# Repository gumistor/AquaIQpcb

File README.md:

# AquaIQpcb
Mini computer to control a sea tank. Based on LPC1769Board.

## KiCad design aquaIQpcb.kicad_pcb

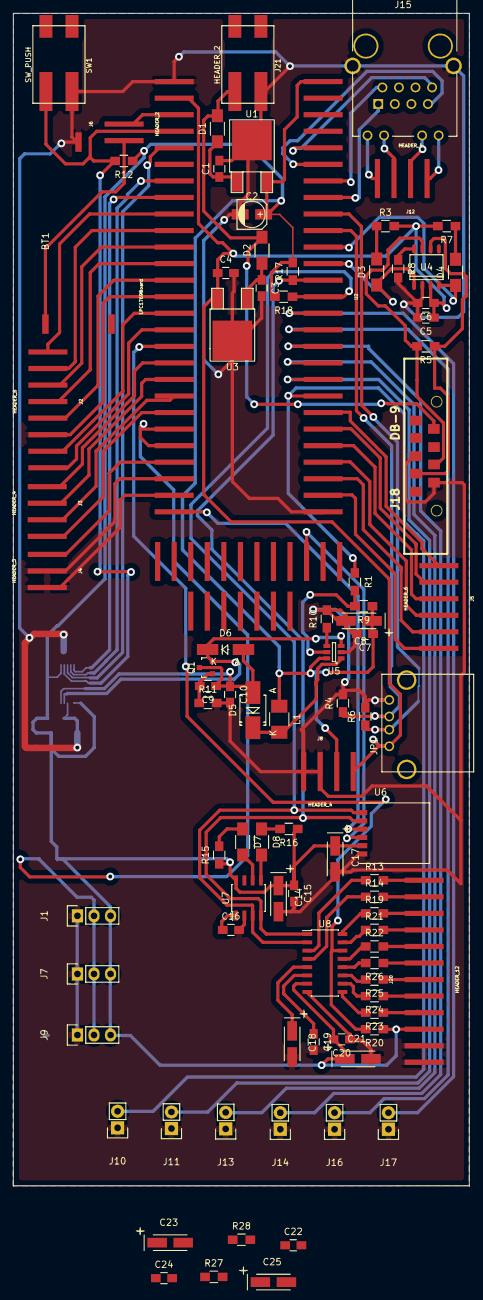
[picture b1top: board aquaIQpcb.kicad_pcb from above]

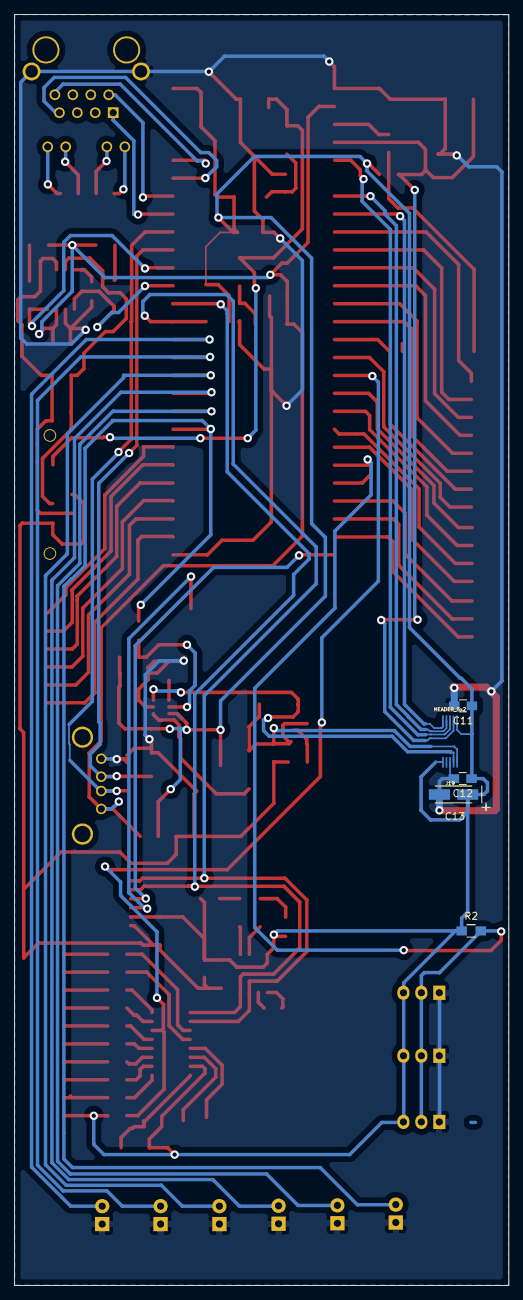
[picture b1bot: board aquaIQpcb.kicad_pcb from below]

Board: 2 copper layers, 70.0 x 180.0 mm, 95 parts (5 on the bottom side), 91 nets.

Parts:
BT1: Battery; BATTERY_3.6_05AA
C1, C3: 330n; C_0805_HandSoldering
C2: 10uF; c_elec_4x5.3
C4, C5, C6, C7, C20, C22: 100n; C_0805_HandSoldering
C8: 22u/6.3V; TantalC_SizeA_EIA-3216_HandSoldering
C9: 47nF; C_0805_HandSoldering
C10: 1u/25V; C_0805_HandSoldering
C11, C12, C15, C16, C19: 100nF; C_0805_HandSoldering
C13, C14, C17: 22uF/6.3V; TantalC_SizeA_EIA-3216_HandSoldering
C18: 2.2uF/5V; TantalC_SizeA_EIA-3216_HandSoldering
C21: 1u; TantalC_SizeA_EIA-3216_HandSoldering
C23: 1uF/6.3V; TantalC_SizeA_EIA-3216_HandSoldering
C24: 10nF; C_0805_HandSoldering
C25: 2.2uF/6.3V; TantalC_SizeA_EIA-3216_HandSoldering
D1, D2: D; R_1206_HandSoldering
D3, D4: LED; R_1206_HandSoldering
D5: D_Schottky; Diode-SMB_Handsoldering
D6: 24V; Diode-MiniMELF_Handsoldering
D7: GREEN; R_1206_HandSoldering
D8: RED; R_1206_HandSoldering
J1, J7, J9: HEADER_3; Pin_Header_Straight_1x03
J2: HEADER_8; HEADER_SMD_1x8
J3, J8, J12: HEADER_4; HEADER_SMD_1x4
J4: HEADER_3; HEADER_SMD_1x3
J5: HEADER_6; HEADER_SMD_1x6
J6: HEADER_2; HEADER_SMD_1x2
J10, J11, J13, J14, J16, J17: HEADER_2; Pin_Header_Straight_1x02
J15: rj45; RJ45_TRANSFO
J18: DB-9; DB9SMD_oneside
J19: HEADER_5x2; HIROSE_DF23C-10
J20: HEADER_12; HEADER_SMD_1x12
J21: HEADER_2; MOLEX_LITETRAPS_2
JP1: USB-A; USB_A
L1: 6.8uH; R_1210_HandSoldering
Q1: MMBT3904; SOT-23
R1: 0R; R_0805_HandSoldering
R2, R17, R18: 4k7; R_0805_HandSoldering
R3, R7: 1k; R_0805_HandSoldering
R4, R6: 15k; R_0805_HandSoldering
R5: 120; R_0805_HandSoldering
R8: 47k; R_0805_HandSoldering
R9, R12, R20: 10k; R_0805_HandSoldering
R10, R11: 1k5; R_0805_HandSoldering
R13, R14, R19, R21, R22: 560; R_0805_HandSoldering
R15, R16, R23, R24, R25, R26: 100; R_0805_HandSoldering
R27, R28: 270; R_0805_HandSoldering
SW1: SW_PUSH; MOLEX_LITETRAPS_2
U1: LF33CDT; DPAK-2
U2: LPC1769Board; LPCXPRESSO_LPC1769
U3: 7805; DPAK-2
U4: MCP2551-I/SN; SO-8
U5: LT1932; SOT-23-6
U6: HP02S
U7: HIH6131; SOIC-8_3.9x4.9mm_Pitch1.27mm
U8: CY8CMBR3110; SOIC-16_3.9x9.9mm_Pitch1.27mm

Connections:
+3V3: C2.1, C7.1, C8.1, C11.1, C12.1, C13.1, C17.1, C20.2, C21.1, C22.2, J1.3, J7.3, J8.3, J9.3, J15.3, J19.1, J19.6, J20.3, L1.1, R2.1, R9.1, R12.1, R17.2, R18.2, R20.1, R27.2, R28.2, U1.3, U2.28, U5.6, U6.5, U8.7
+5V: C4.1, C5.1, C6.1, C23.1, J8.4, JP1.1, R3.2, R7.2, U2.2, U4.3
+12V: D1.2, D2.2, J18.9, J21.2
/D+: JP1.3, R4.1, U2.37
/D-: JP1.2, R6.1, U2.36
/I2Csensors/AL_H#: D8.1, U7.5
/I2Csensors/AL_L#: D7.1, U7.6
/I2Csensors/D1: J20.4, R23.1
/I2Csensors/D2: J20.5, R24.1
/I2Csensors/D3: J20.6, R25.1
/I2Csensors/D4: J20.7, R26.1
/I2Csensors/MBR3_IRQ#: R20.2, U2.17, U8.14
/I2Csensors/PROX: J20.12, R13.2
/I2Csensors/S1: J20.11, R14.2
/I2Csensors/S2: J20.8, R22.2
/I2Csensors/S3: J20.9, R21.2
/I2Csensors/S4: J20.10, R19.2
/I2Csensors/SENS_HP02S_MCLK: U2.PD10, U6.4
/I2Csensors/SENS_HP02S_XCLR: U2.27, U6.3
/I2Csensors/SENS_I2C_SCL: R18.1, U2.41, U6.1, U7.3, U8.2
/I2Csensors/SENS_I2C_SDA: R17.1, U2.40, U6.2, U7.4, U8.1
/Nokia6100LCD/LCD_LED+: C9.1, C10.1, D5.1, D6.2, J19.10, Q1.2
/Nokia6100LCD/LCD_LED-: D6.1, J19.9, Q1.3, U5.3
/Nokia6100LCD/LCD_RESET_N: J19.2, R12.2, SW1.2, U2.4
/Nokia6100LCD/LCD_SPI_MOSI: J19.3, U2.5
/Nokia6100LCD/LCD_SPI_SCK: J19.4, U2.7
/Nokia6100LCD/LCD_SPI_SSEL: J19.5, U2.8
/Nokia6100LCD/PWM: R1.2, R9.2, U5.5
/RJ45_L2: J12.2, J15.YK, U2.25
/RJ45_L4: J12.4, J15.GK, U2.26
/VBatt: J6.2, U2.3
/can_rx: D4.1, U2.38, U4.4
/can_tx: D3.1, U2.39, U4.1
/canh: J18.7, R5.2, U4.7
/canl: J18.2, R5.1, U4.6
/eth_rd+: J15.7, U2.33
/eth_rd-: J15.8, U2.32
/eth_td+: J15.1, U2.35
/eth_td-: J15.2, U2.34
/h1_1: J2.1, U2.9
/h1_2: J2.2, U2.10
/h1_3: J2.3, U2.11
/h1_4: J2.4, U2.12
/h1_5: J2.5, U2.13
/h1_7: J2.7, U2.15
/h1_8: J2.8, U2.16
/h2_1: J3.1, U2.18
/h2_2: J3.2, U2.19
/h2_3: J3.3, U2.20
/h2_4: J3.4, U2.21
/h3_1: J4.1, U2.24
/h4_1: J5.1, U2.48
/h4_2: J5.2, U2.49
/h4_3: J5.3, U2.50
/h4_4: J5.4, U2.51
/h4_5: J5.5, U2.52
/h4_6: J5.6, U2.53
/oneWire: J1.2, J7.2, J9.2, R2.2, U2.22, U2.23
/pwm1_1: J17.2, U2.42
/pwm1_2: J16.2, U2.43
/pwm1_3: J14.2, U2.44
/pwm1_4: J13.2, U2.45
/pwm1_5: J11.2, U2.46
/pwm1_6: J10.2, R1.1, U2.47
GND: BT1.2, C1.2, C2.2, C3.2, C4.2, C5.2, C6.2, C7.2, C8.2, C10.2, C11.2, C12.2, C13.2, C14.2, C15.2, C16.2, C17.2, C18.2, C19.2, C20.1, C21.2, C22.1, C23.2, C24.2, C25.2, J1.1, J2.6, J4.2, J4.3, J7.1, J8.1, J8.2, J9.1, J10.1, J11.1, J13.1, J14.1, J15.13, J16.1, J17.1, J18.3, J18.6, J19.8, J20.1, J20.2, J21.1, JP1.4, R4.2, R6.2, R8.2, R10.2, R11.2, SW1.1, U1.2, U2.1, U2.54, U4.2, U5.2, U6.6, U7.2, U8.8
unnamed: BT1.1, J6.1
unnamed: C1.1, D1.1, U1.1
unnamed: C3.1, D2.1
unnamed: C9.2, Q1.1, R11.1
unnamed: C14.1, C15.1, C25.1, R15.1, R16.1, U7.8
unnamed: C16.1, U7.1
unnamed: C18.1, U8.5
unnamed: C19.1, U8.6
unnamed: D3.2, R3.1
unnamed: D4.2, R7.1
unnamed: D5.2, L1.2, U5.1
unnamed: D7.2, R15.2
unnamed: D8.2, R16.2
unnamed: J15.GA, R28.1
unnamed: J15.YA, R27.1
unnamed: R8.1, U4.8
unnamed: R10.1, U5.4
unnamed: R13.1, U8.3
unnamed: R14.1, U8.4
unnamed: R19.1, U8.16
unnamed: R21.1, U8.15
unnamed: R22.1, U8.13
unnamed: R23.2, U8.9
unnamed: R24.2, U8.10
unnamed: R25.2, U8.11
unnamed: R26.2, U8.12

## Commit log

2021-11-25 Initial version.
2021-11-25 Libraries added.
